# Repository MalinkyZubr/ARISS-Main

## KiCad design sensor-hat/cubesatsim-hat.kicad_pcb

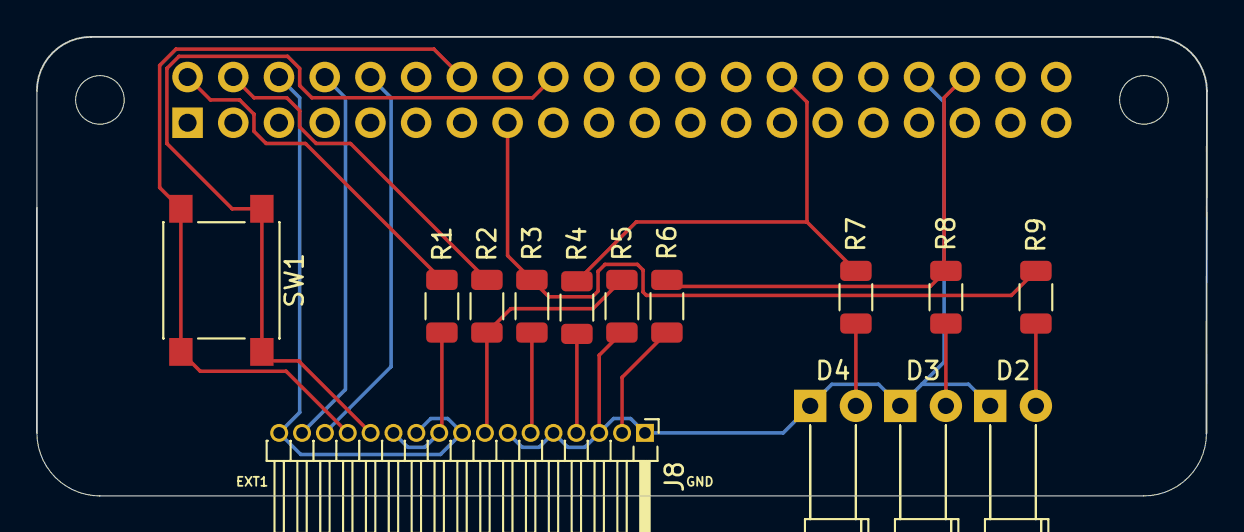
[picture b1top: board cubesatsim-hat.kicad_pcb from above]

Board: 2 copper layers, 65.0 x 25.5 mm, 17 parts (1 on the bottom side), 19 nets.

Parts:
D2, D3, D4: LED; LED_D3.0mm_Horizontal_O6.35mm_Z10.0mm
J1: GPIO; PinSocket_2x20_P2.54mm_Vertical
J8: Conn_01x17_Pin; PinHeader_1x17_P1.27mm_Horizontal
MH1, MH2: MountingHole_2.7mm_M2.5
R1, R3, R4, R6, R7, R8, R9: 1000; R_1206_3216Metric
R2, R5: 10000; R_1206_3216Metric
SW1: SW_SPST; SW_Push_1P1T_NO_6x6mm_H9.5mm

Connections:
unnamed: D2.2 (A), R9.2
unnamed: D2.1 (K), D3.1 (K), D4.1 (K), J1.34, J8.1, J8.3, J8.5, J8.7, R5.2
unnamed: D3.2 (A), R8.1
unnamed: D4.2 (A), R7.2
unnamed: J1.2, R1.1
unnamed: J1.4, R2.1
unnamed: J1.6, J8.9, J8.11, J8.17
unnamed: J1.8, J8.16
unnamed: J1.10, J8.15
unnamed: J1.14, J8.14, SW1.2
unnamed: J1.15, R3.1, R9.1
unnamed: J1.18, J8.13, SW1.1
unnamed: J1.28, R4.1, R7.1
unnamed: J1.36, R6.1, R8.2
unnamed: J8.2, R6.2
unnamed: J8.4, R4.2
unnamed: J8.6, R3.2
unnamed: J8.8, R2.2, R5.1
unnamed: J8.10, J8.12, R1.2

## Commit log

2024-05-30 added hackrf images for portsdown ugly
2024-05-30 update changelog
2024-05-30 committed things
2024-05-30 updated changelog
2024-06-01 changelog updates
2024-06-03 changelog
2024-06-05 working
2024-06-11 work
2024-07-03 updated picotuner tests
2024-07-07 picotuner tests
2024-07-08 stuff
2024-07-09 cmmit
2024-07-09 dave questions
2024-07-15 rebase
2024-07-17 reorganize
2024-07-22 blinker
2024-07-22 modded crontab
2024-07-24 moved stuff around
2024-07-25 changes:
2024-07-25 silly
2024-07-25 change
2024-07-25 FIXED
2024-07-29 pluto guide
2024-08-05 reorganization
